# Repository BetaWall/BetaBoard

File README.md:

*Chat to the devs on [Telegram](https://t.me/joinchat/AAAAAAxiRIuuax58XAVMrQ).*

A multiplexed APA102 LED driver board for the BetaWall system.

## Features

- Input runs through a single RJ45 connector via RS-485 protocol.
- Outputs SPI to APA102 LEDs.
- Supports up to 32 strips of 256 LEDs.
- Supports daisychaining of up to 128 BetaBoards to drive a total of over 1 Million LEDs.

## Block Diagram

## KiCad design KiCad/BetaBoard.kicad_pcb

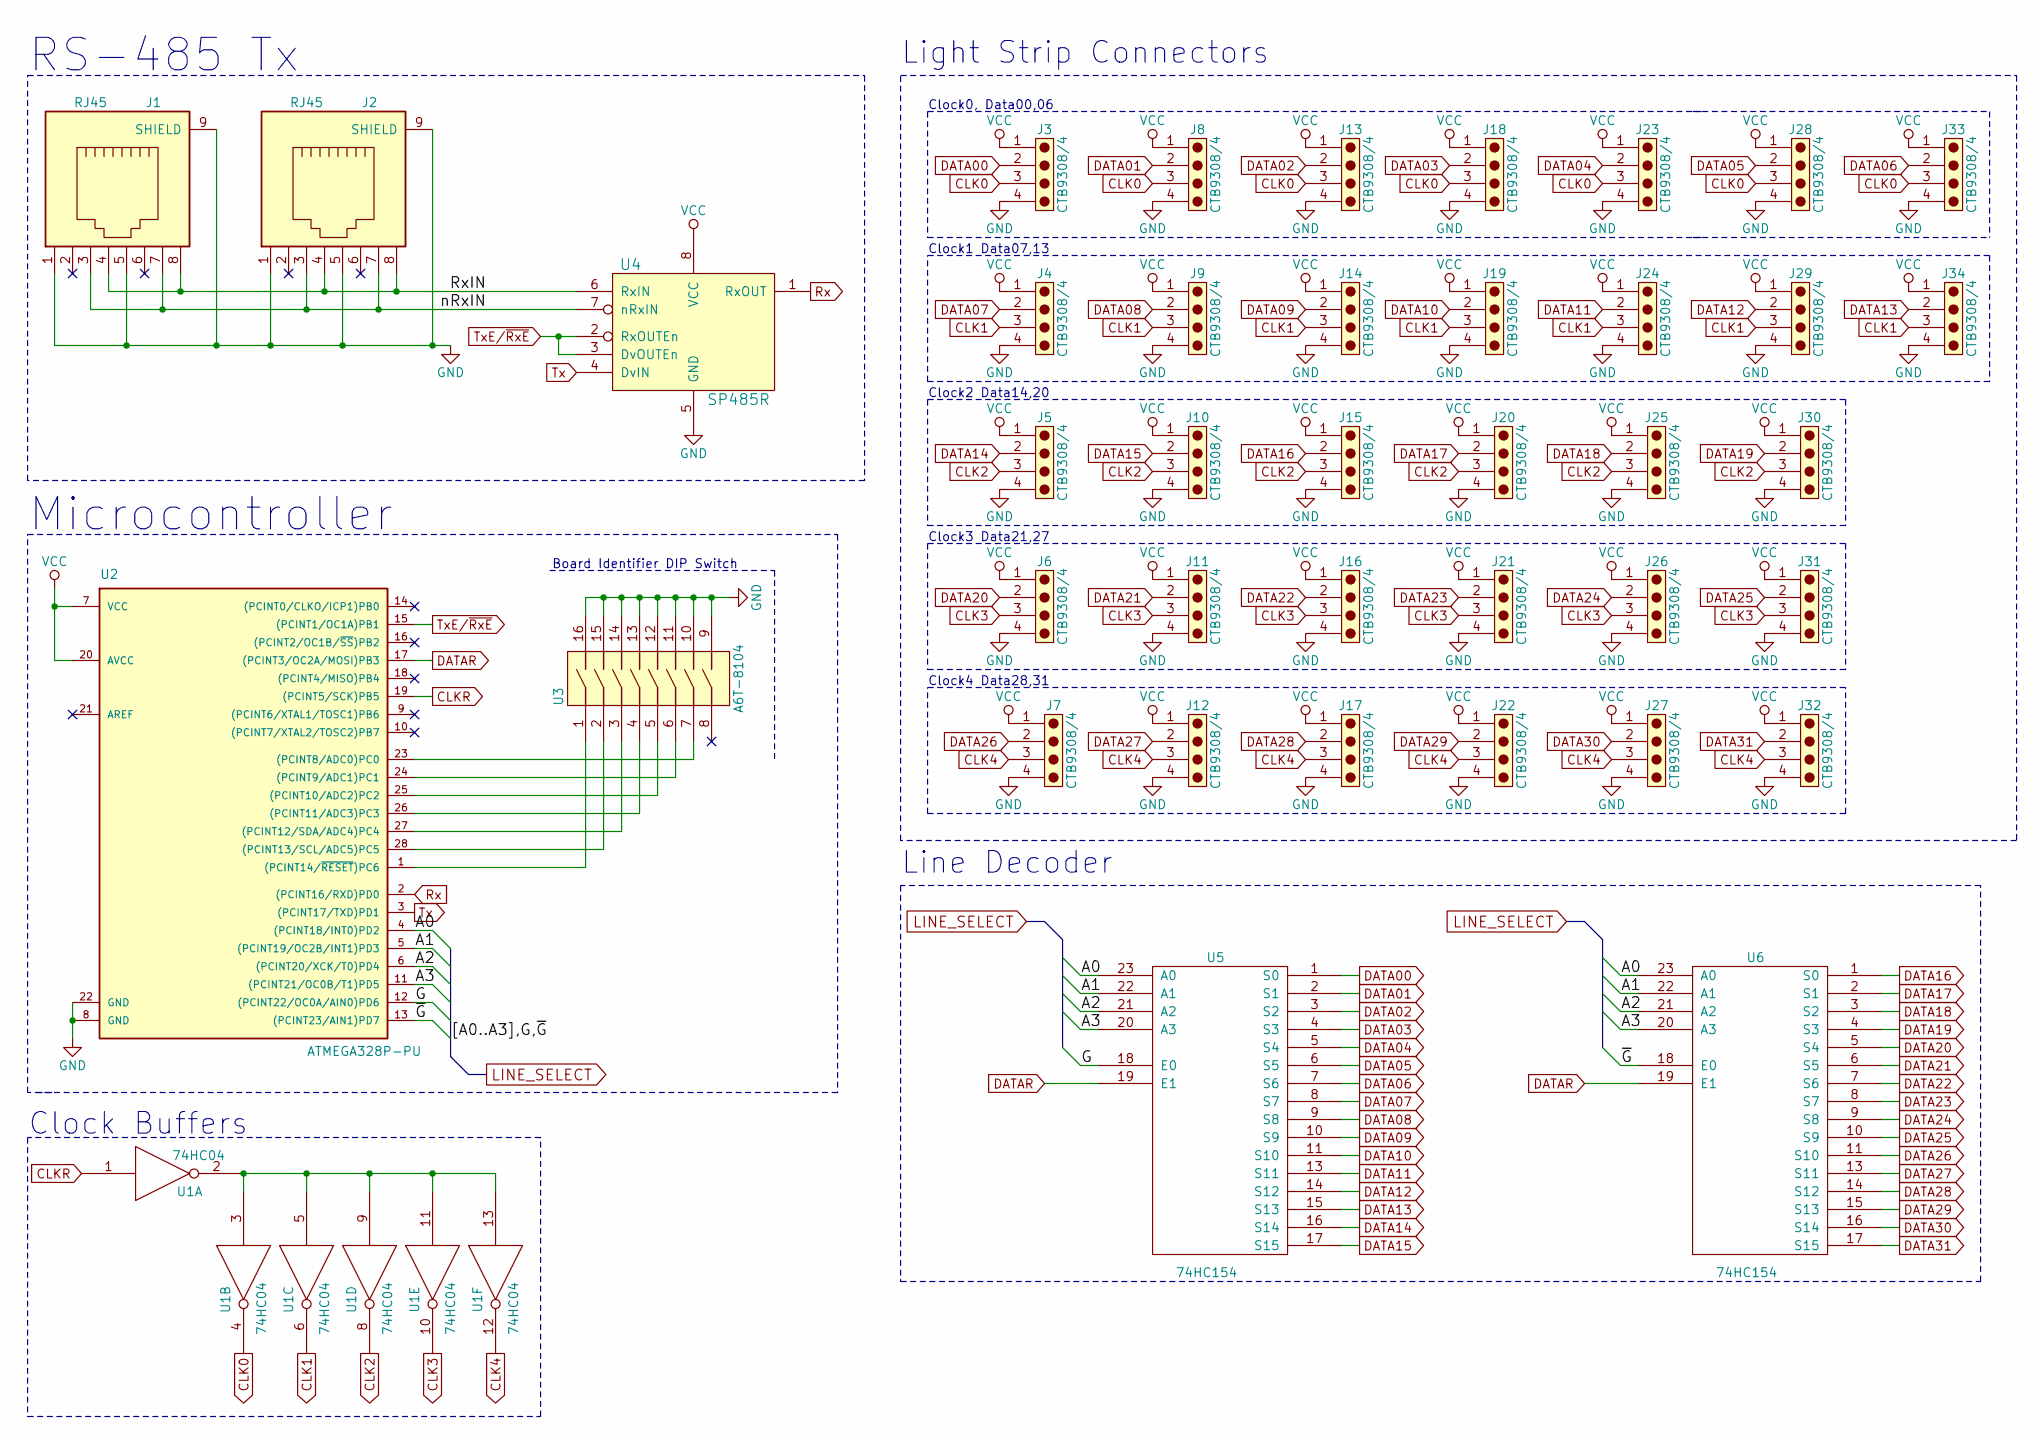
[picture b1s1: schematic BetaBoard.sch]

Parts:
J1, J2: RJ45; RJ45_TRANSFO_ver2
J3, J4, J5, J6, J7, J8, J9, J10, J11, J12, J13, J14, J15, J16, J17, J18, J19, J20, J21, J22, J23, J24, J25, J26, J27, J28, J29, J30, J31, J32, J33, J34: CTB9308/4; TerminalBlock_Pheonix_MPT-2.54mm_4pol
U1: 74HC04; DIP-14_W7.62mm_Socket_LongPads
U2: ATMEGA328P-PU; DIP-28_W7.62mm_Socket_LongPads
U3: A6T-8104; DIP-16_W7.62mm_Socket_LongPads
U4: SP485R; DIP-8_W7.62mm_Socket_LongPads
U5, U6: 74HC154; DIP-24_W7.62mm_Socket_LongPads

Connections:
/A0: U2.4 ((PCINT18/INT0)PD2), U5.23 (A0), U6.23 (A0)
/A1: U2.5 ((PCINT19/OC2B/INT1)PD3), U5.22 (A1), U6.22 (A1)
/A2: U2.6 ((PCINT20/XCK/T0)PD4), U5.21 (A2), U6.21 (A2)
/A3: U2.11 ((PCINT21/OC0B/T1)PD5), U5.20 (A3), U6.20 (A3)
/G: U2.12 ((PCINT22/OC0A/AIN0)PD6), U5.18 (E0)
/RxIN: J1.4, J1.8, J2.4, J2.8, U4.6 (RxIN)
/nRxIN: J1.3, J1.7, J2.3, J2.7, U4.7 (nRxIN)
/~G: U2.13 ((PCINT23/AIN1)PD7), U6.18 (E0)
CLK0: J3.3, J8.3, J13.3, J18.3, J23.3, J28.3, J33.3, U1.4
CLK1: J4.3, J9.3, J14.3, J19.3, J24.3, J29.3, J34.3, U1.6
CLK2: J5.3, J10.3, J15.3, J20.3, J25.3, J30.3, U1.8
CLK3: J6.3, J11.3, J16.3, J21.3, J26.3, J31.3, U1.10
CLK4: J7.3, J12.3, J17.3, J22.3, J27.3, J32.3, U1.12
CLKR: U1.1, U2.19 ((PCINT5/SCK)PB5)
DATA00: J3.2, U5.1 (S0)
DATA01: J8.2, U5.2 (S1)
DATA02: J13.2, U5.3 (S2)
DATA03: J18.2, U5.4 (S3)
DATA04: J23.2, U5.5 (S4)
DATA05: J28.2, U5.6 (S5)
DATA06: J33.2, U5.7 (S6)
DATA07: J4.2, U5.8 (S7)
DATA08: J9.2, U5.9 (S8)
DATA09: J14.2, U5.10 (S9)
DATA10: J19.2, U5.11 (S10)
DATA11: J24.2, U5.13 (S11)
DATA12: J29.2, U5.14 (S12)
DATA13: J34.2, U5.15 (S13)
DATA14: J5.2, U5.16 (S14)
DATA15: J10.2, U5.17 (S15)
DATA16: J15.2, U6.1 (S0)
DATA17: J20.2, U6.2 (S1)
DATA18: J25.2, U6.3 (S2)
DATA19: J30.2, U6.4 (S3)
DATA20: J6.2, U6.5 (S4)
DATA21: J11.2, U6.6 (S5)
DATA22: J16.2, U6.7 (S6)
DATA23: J21.2, U6.8 (S7)
DATA24: J26.2, U6.9 (S8)
DATA25: J31.2, U6.10 (S9)
DATA26: J7.2, U6.11 (S10)
DATA27: J12.2, U6.13 (S11)
DATA28: J17.2, U6.14 (S12)
DATA29: J22.2, U6.15 (S13)
DATA30: J27.2, U6.16 (S14)
DATA31: J32.2, U6.17 (S15)
DATAR: U2.17 ((PCINT3/OC2A/MOSI)PB3), U5.19 (E1), U6.19 (E1)
GND: J1.1, J1.5, J1.9 (SHIELD), J2.1, J2.5, J2.9 (SHIELD), J3.4, J4.4, J5.4, J6.4, J7.4, J8.4, J9.4, J10.4, J11.4, J12.4, J13.4, J14.4, J15.4, J16.4, J17.4, J18.4, J19.4, J20.4, J21.4, J22.4, J23.4, J24.4, J25.4, J26.4, J27.4, J28.4, J29.4, J30.4, J31.4, J32.4, J33.4, J34.4, U1.7 (GND), U2.8 (GND), U2.22 (GND), U3.9, U3.10, U3.11, U3.12, U3.13, U3.14, U3.15, U3.16, U4.5 (GND), U5.12 (GND), U6.12 (GND)
unnamed: U1.2, U1.3, U1.5, U1.9, U1.11, U1.13
unnamed: U2.1 ((PCINT14/~RESET~)PC6), U3.1
unnamed: U2.23 ((PCINT8/ADC0)PC0), U3.7
unnamed: U2.24 ((PCINT9/ADC1)PC1), U3.6
unnamed: U2.25 ((PCINT10/ADC2)PC2), U3.5
unnamed: U2.26 ((PCINT11/ADC3)PC3), U3.4
unnamed: U2.27 ((PCINT12/SDA/ADC4)PC4), U3.3
unnamed: U2.28 ((PCINT13/SCL/ADC5)PC5), U3.2
Rx: U2.2 ((PCINT16/RXD)PD0), U4.1 (RxOUT)
Tx: U2.3 ((PCINT17/TXD)PD1), U4.4 (DvIN)
TxE/~RxE: U2.15 ((PCINT1/OC1A)PB1), U4.2 (RxOUTEn), U4.3 (DvOUTEn)
VCC: J3.1, J4.1, J5.1, J6.1, J7.1, J8.1, J9.1, J10.1, J11.1, J12.1, J13.1, J14.1, J15.1, J16.1, J17.1, J18.1, J19.1, J20.1, J21.1, J22.1, J23.1, J24.1, J25.1, J26.1, J27.1, J28.1, J29.1, J30.1, J31.1, J32.1, J33.1, J34.1, U1.14 (VCC), U2.7 (VCC), U2.20 (AVCC), U4.8 (VCC), U5.24 (VCC)

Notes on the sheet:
RS-485 Tx
Board Identifier DIP Switch
Microcontroller
Clock0, Data00,06
Clock1 Data07,13
Clock2 Data14,20
Clock3 Data21,27
Clock4 Data28,31
Clock Buffers
Light Strip Connectors
Line Decoder

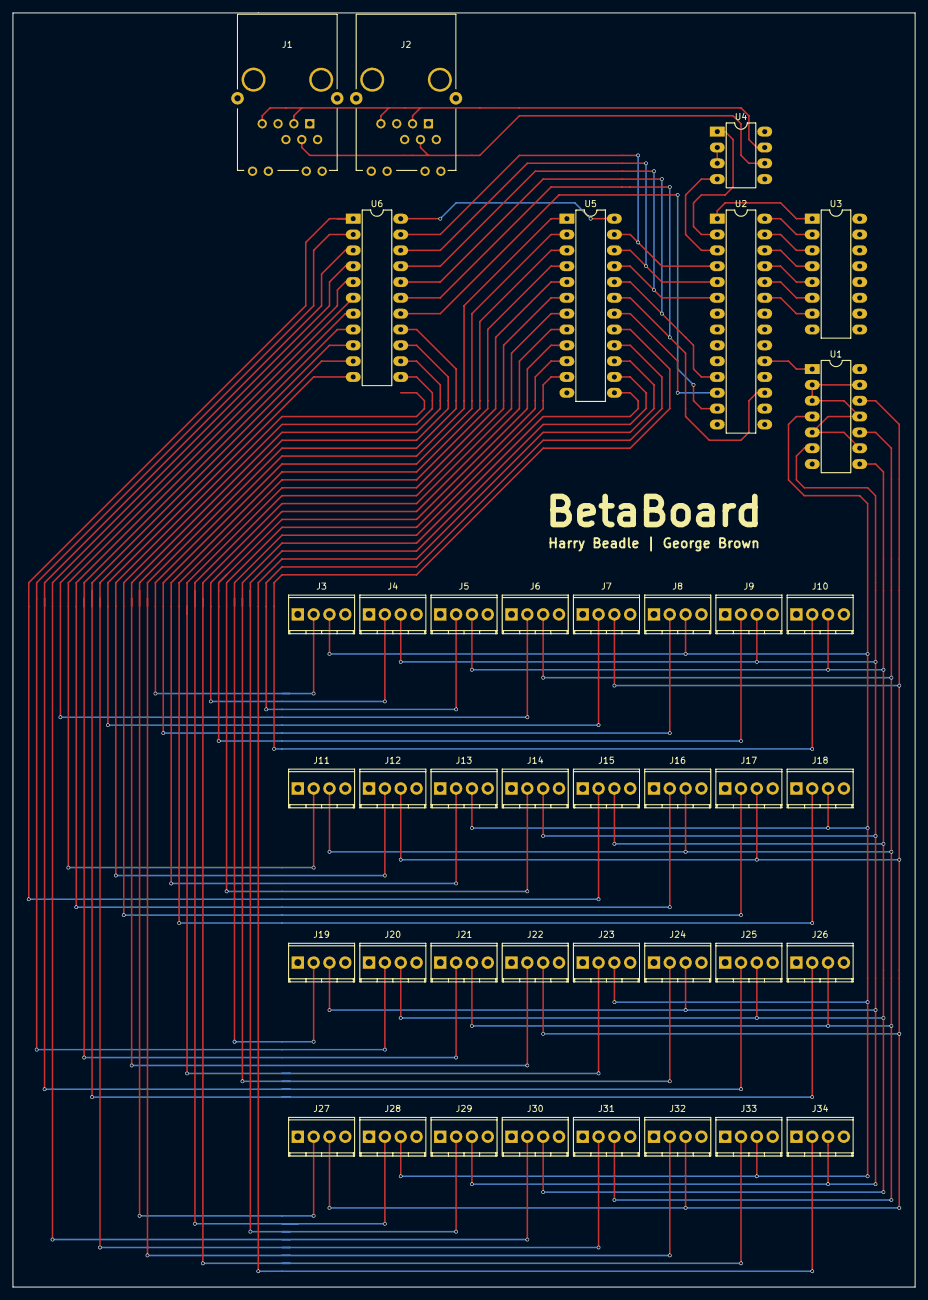
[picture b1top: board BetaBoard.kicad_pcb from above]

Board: 2 copper layers, 144.8 x 204.5 mm, 40 parts (0 on the bottom side), 60 nets.

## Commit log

2017-01-30 init
2017-01-31 Update LICENCE
    Change to AGPL
2017-01-31 + Early code for testing the LED arrays. Driven by Raspberry pi SPI peripheral.
2017-01-31 * Update Licence logo to AGPL
2017-01-31 Add block diagram
2017-01-31 Documentation
2017-02-02 gitignore for un-important TeX output files
2017-02-03 Add testing suite
2017-02-03 add framerate graph
2017-02-04 more testing
2017-02-05 Inital AVR code
2017-05-05 Started Schematic Entry
    Input Communications
    RJ45 Connector
    RS-485 Decoder
    Controller
    Microcontroller
    DIP Switch for Board ID
2017-05-05 Updated to reflect changes in project direction
2017-05-05 Added PDF plot of Schematic
2017-05-05 Added telegram link
2017-07-14 +Add per channel decoder. *Spread out the clock drivers more evenly. *Misc tidy up.
2017-08-14 + Layout
2017-08-14 +Silkscreen/EdgeCuts *DRM Fails

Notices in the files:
README.md:
AGPLv3
